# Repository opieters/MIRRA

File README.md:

# MIRRA 

Microclimate Instrument for Real-time Remote Applications

⚠️ This is a research project. Limited testing has been performed and reliability of data storage/sensor readout is not guaranteed. Use with caution. ⚠️

## 3D Designs

The radiation is 3D printed and designed using OpenSCAD. All design files can eb found in `3d_printing`. They can be printed using an extrusion printer, with minimal post-processign (no supports).

## PCB designs

All PCBs are designed with KiCAD and located in the `pcb_boards` directory. Components also contain ordering codes for Mouser and/or Farnell, such that the design is completely rebuilable.

## Embedded Code

The software for the sensor node and gateway are located in the `firmware` folder. The easiest way to build and upload the code is using PlaformIO. 

## Server / web-interface

Use docker-compose to start the webserver and related components (such as MQTT server, graphena...) from the `webserver` folder. Some services are password protected, the passwords are (for now) also included in the docker-compose file.

## Licence

Apache-2.0 License, see LICENSE file.

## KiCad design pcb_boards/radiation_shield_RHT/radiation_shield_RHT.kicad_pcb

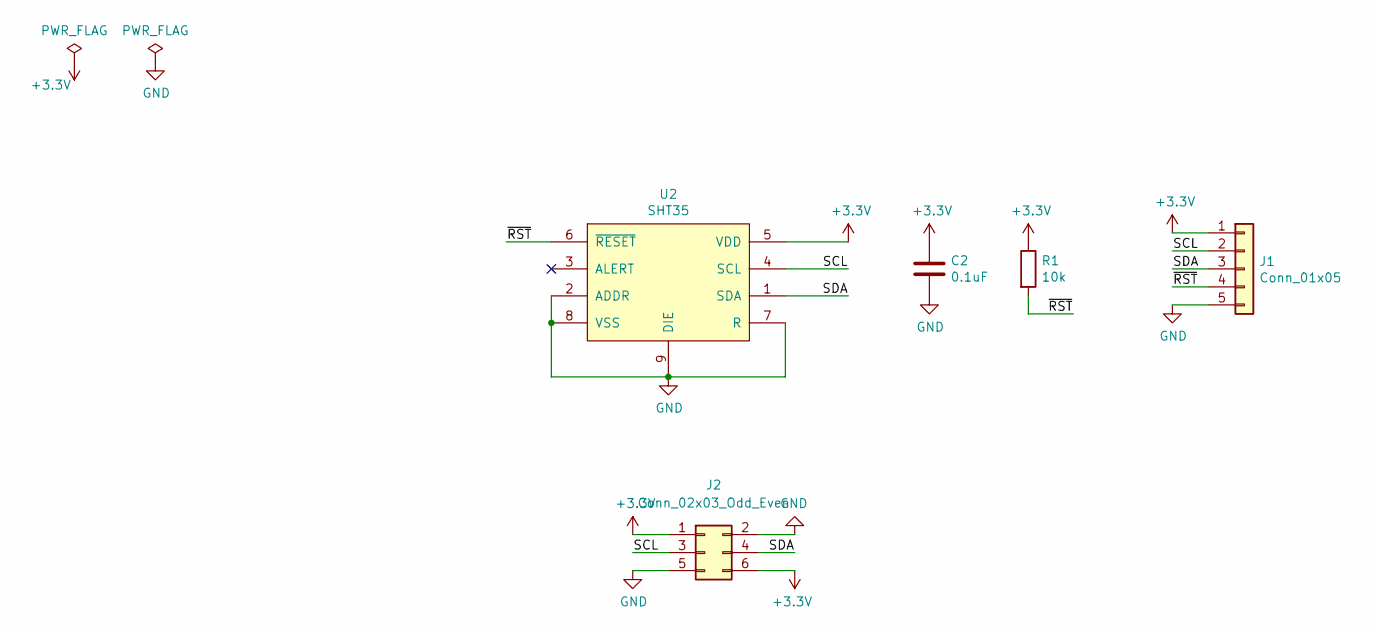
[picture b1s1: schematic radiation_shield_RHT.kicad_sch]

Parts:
C2: 0.1uF; C_0603_1608Metric; Mouser 810-CGA3E2X8R1E104K
J1: Conn_01x05; JST_XH_B05B-XH-A_1x05_P2.50mm_Vertical; Mouser Farnell: 1516281
J2: Conn_02x03_Odd_Even; PinHeader_2x03_P2.54mm_Vertical; Mouser 538-10-88-3061
R1: 10k; R_0603_1608Metric; Mouser 284-APC0603B10K0N
U2: SHT35; 8P-1EP-DFN_2.5x2.5; Mouser 403-SHT35-DIS-F

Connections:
+3V3: C2.1, J1.1, J2.1, J2.6, R1.1, U2.5 (VDD)
/SCL: J1.2, J2.3, U2.4 (SCL)
/SDA: J1.3, J2.4, U2.1 (SDA)
/~RST: J1.4, R1.2, U2.6 (~RESET)
GND: C2.2, J1.5, J2.2, J2.5, U2.2 (ADDR), U2.7 (R), U2.8 (VSS), U2.9 (DIE)

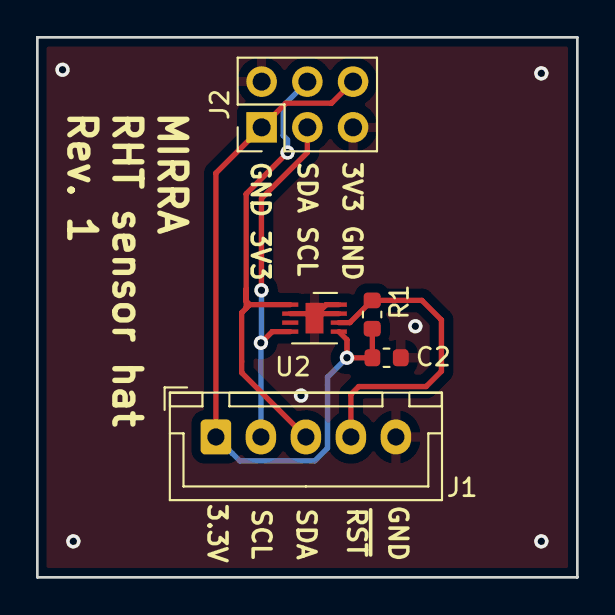
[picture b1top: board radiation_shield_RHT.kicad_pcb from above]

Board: 2 copper layers, 30.0 x 30.0 mm, 5 parts (0 on the bottom side), 5 nets.

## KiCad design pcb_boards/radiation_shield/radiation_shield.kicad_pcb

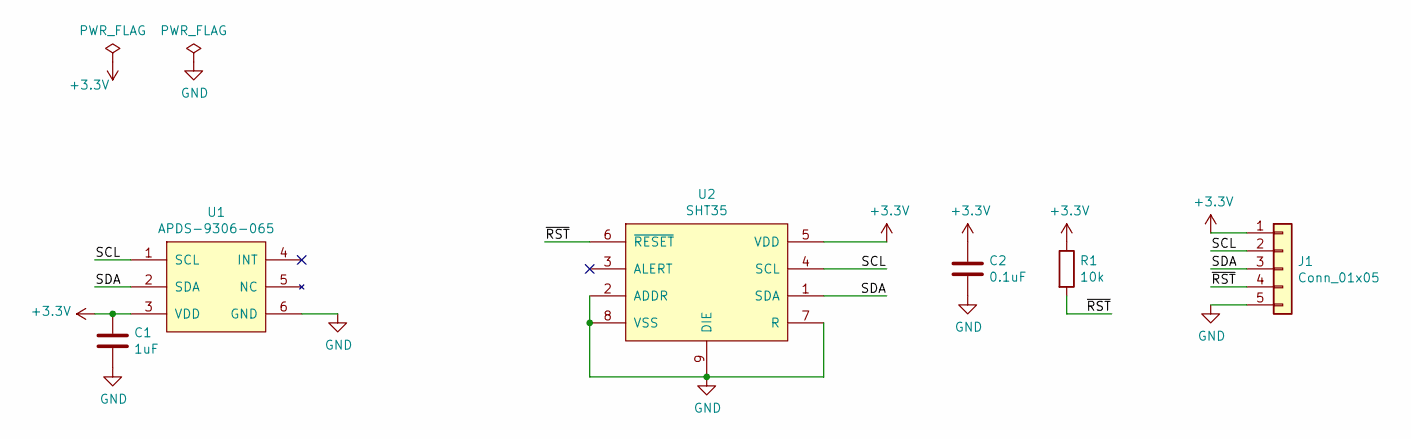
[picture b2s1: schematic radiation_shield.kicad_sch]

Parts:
C1: 1uF; C_0603_1608Metric; Mouser 710-885012206083
C2: 0.1uF; C_0603_1608Metric; Mouser 810-CGA3E2X8R1E104K
J1: Conn_01x05; JST_XH_B05B-XH-A_1x05_P2.50mm_Vertical; Mouser Farnell: 1516281
R1: 10k; R_0603_1608Metric; Mouser 284-APC0603B10K0N
U1: APDS-9306-065; Mouser 630-APDS-9306-065
U2: SHT35; 8P-1EP-DFN_2.5x2.5; Mouser 403-SHT35-DIS-F

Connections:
+3V3: C1.1, C2.1, J1.1, R1.1, U1.3 (VDD), U2.5 (VDD)
/SCL: J1.2, U1.1 (SCL), U2.4 (SCL)
/SDA: J1.3, U1.2 (SDA), U2.1 (SDA)
/~RST: J1.4, R1.2, U2.6 (~RESET)
GND: C1.2, C2.2, J1.5, U1.6 (GND), U2.2 (ADDR), U2.7 (R), U2.8 (VSS), U2.9 (DIE)

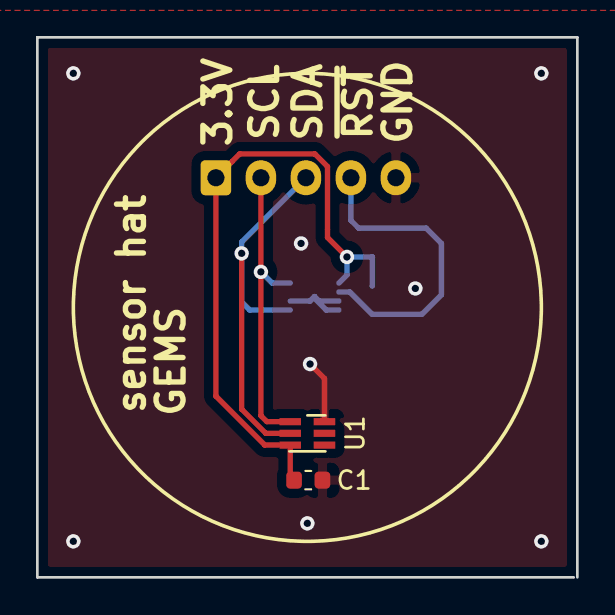
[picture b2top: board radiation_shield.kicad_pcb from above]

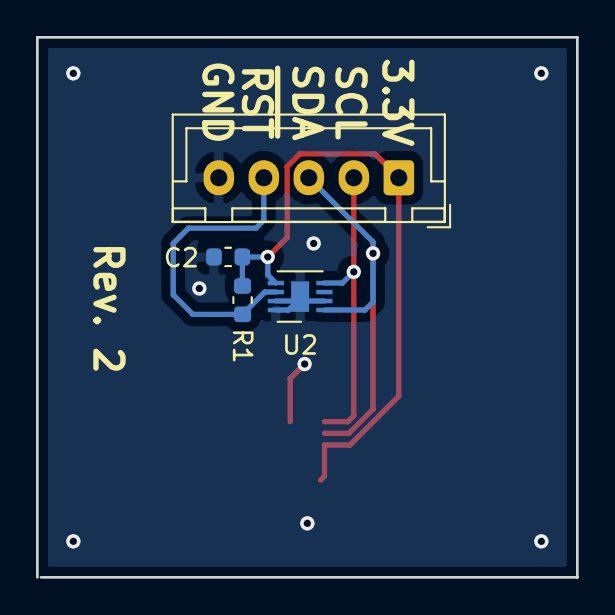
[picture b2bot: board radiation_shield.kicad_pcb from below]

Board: 2 copper layers, 30.0 x 30.0 mm, 6 parts (4 on the bottom side), 5 nets.

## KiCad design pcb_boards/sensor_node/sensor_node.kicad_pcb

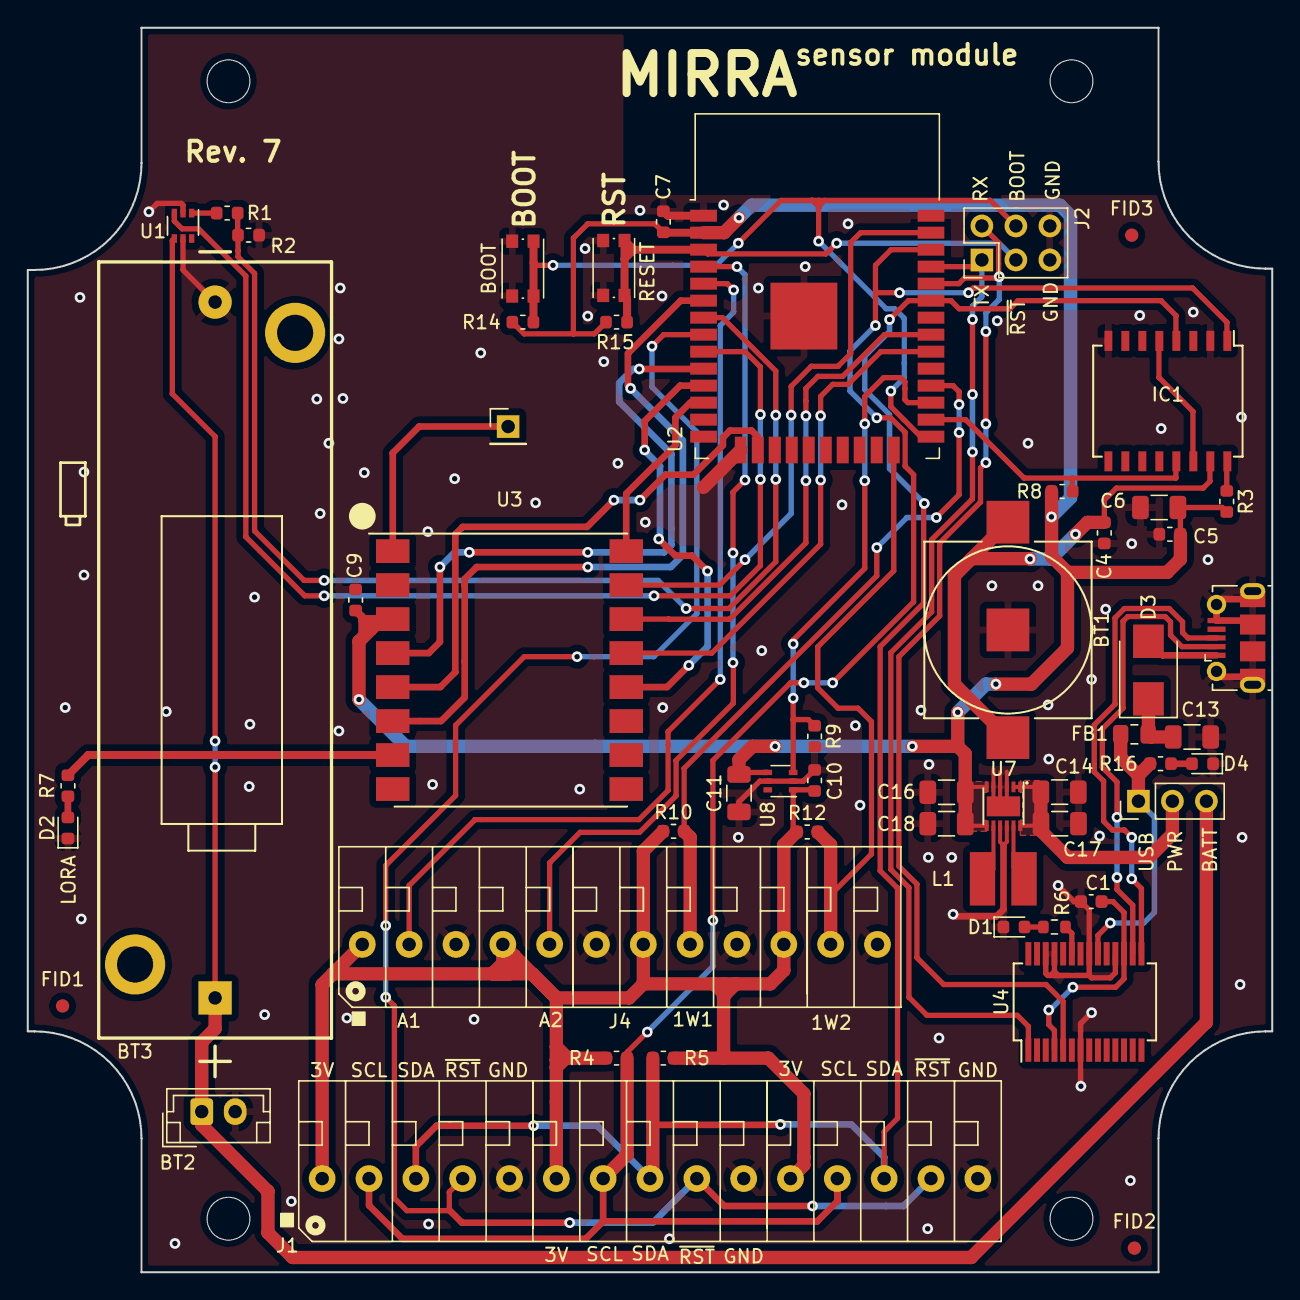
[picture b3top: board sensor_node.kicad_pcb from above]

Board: 2 copper layers, 93.0 x 93.0 mm, 58 parts (0 on the bottom side), 46 nets.

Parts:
AE1: Antenna; PinHeader_1x01_P2.54mm_Vertical
BT1: Battery_Cell; Renata_Battery_Holder_SMTM1125
BT2: Battery_Cell; JST_EH_B02B-EH-A_1x02_P2.50mm_Vertical
BT3: Battery_Cell; Eagle_Battery_Holder_A_12BH311P-GR
C1, C4, C5, C7, C9, C10: 100nF; C_0603_1608Metric
C6, C11: 6.8µF; C_1206_3216Metric
C13, C14, C17: 10uF; C_1206_3216Metric
C16, C18: 22uF; C_1206_3216Metric
D1, D2, D4: LED; LED_0603_1608Metric
D3: D_Schottky; D_SMB
FB1: Ferrite_Bead; L_0805_2012Metric_Pad1.15x1.40mm_HandSolder
FID1, FID2, FID3: Fiducial; Fiducial_1mm_Mask2mm
H1, H2, H3, H4: MountingHole; MountingHole_3.2mm_M3
IC1: PCF2129T; SO16
IO4: BOOT; SW_SPST_KMR2
J1: Screw_Terminal_01x15; TerminalBlock_Phoenix_PTSA-1,2-2-3,5-F-THR-1x15-P3.50mm_45D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
J2: Conn_02x03_Odd_Even; PinHeader_2x03_P2.54mm_Vertical
J3: USB_B_Micro; USB_Micro-B_Molex-105017-0001
J4: Screw_Terminal_01x12; TerminalBlock_Phoenix_PTSA-1,2-2-3,5-F-THR-1x12-P3.50mm_45D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
JP2: Jumper_3_Open; PinHeader_1x03_P2.54mm_Vertical
L1: 2.2uH; L_L4mm_D4mm_H1.8mm
R1, R2, R4, R5, R8, R14, R15: 10k; R_0603_1608Metric
R3: 330R; R_0603_1608Metric
R6: 60R; R_0603_1608Metric
R7, R16: 750R; R_0603_1608Metric
R9: 10M; R_0603_1608Metric
R10, R12: 4.7k; R_0603_1608Metric
RESET1: RESET; SW_SPST_KMR2
U1, U8: SiP32431; SOT-363_SC-70-6
U2: ESP32-WROOM-32
U3: RF-LORA-868-SO; RF-LORA-868-SMT
U4: FT232RL; SSOP-28_5.3x10.2mm_P0.65mm
U7: RP604x; DFN_12_Pin_2.7x3mm_P0.5mm

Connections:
+3.3V: C5.1, C6.2, C7.2, C9.1, C11.1, C16.1, C18.1, R3.2, R8.1, R14.1, R15.1, U2.2 (VDD), U3.3 (VCC), U7.6 (VFB), U7.7 (VOUT), U8.4 (IN)
+BATT: BT2.1 (+), BT3.1 (+), JP2.3 (B), U1.4 (IN)
/A1: J4.2, U2.5 (SENSOR_VN)
/A2: J4.5, U2.4 (SENSOR_VP)
/BATT_M: R1.1, R2.1, U2.7 (IO35)
/BATT_MC: U1.3 (ON/OFF), U2.9 (IO33)
/BBS: IC1.5 (IFS), IC1.14 (BBS)
/BOOT: IO4.1, J2.4, R14.2, U2.25 (IO0)
/D+: J3.3 (D+), U4.15 (USBD+)
/D-: J3.2 (D-), U4.16 (USBD-)
/INT_T: IC1.13 (~INT), R8.2, U2.26 (IO4)
/IRQ: U2.6 (IO34), U3.6 (DIO0)
/MISO: U2.31 (IO19), U3.14 (SDO)
/MOSI: U2.37 (IO23), U3.15 (SDI)
/NSS: U2.12 (IO27), U3.16 (~CS)
/ONE_W1: J4.8, R10.2, U2.28 (IO17)
/ONE_W2: J4.11, R12.2, U2.24 (IO2)
/RX: J2.2, U2.34 (RXD0/IO3), U4.5 (RXD)
/RX_SW: U2.10 (IO25), U3.4 (RX_SW)
/SCK: U2.30 (IO18), U3.13 (SCK)
/SCL: IC1.1 (SCL), J1.2, J1.7, J1.12, R4.1, U2.36 (IO22)
/SDA: IC1.4 (SDA/~CE), J1.3, J1.8, J1.13, R5.1, U2.33 (IO21)
/SPOW: R9.1, U2.27 (IO16), U8.3 (ON/OFF)
/TX: J2.1, U2.35 (TXD0/IO1), U4.1 (TXD)
/TX_SW: U2.16 (IO13), U3.5 (TX_SW)
/~RST_I2C: J1.4, J1.9, J1.14, U2.8 (IO32)
/~RST_RF: U2.11 (IO26), U3.12 (RST)
/~RST: J2.3, R15.2, RESET1.1, U2.3 (EN)
GND: BT1.2 (-), BT2.2 (-), BT3.2 (-), C1.2, C4.1, C5.2, C6.1, C7.1, C9.2, C10.2, C11.2, C13.1, C14.1, C16.2, C17.1, C18.2, D1.1 (K), D2.1 (K), D4.1 (K), IC1.2 (SDI), IC1.8 (VSS), IO4.2, J1.5, J1.10, J1.15, J2.5, J2.6, J3.5 (GND), J3.6 (Shield), J4.3, J4.6, J4.9, J4.12, R2.2, R9.2, RESET1.2, U1.2 (GND), U1.5 (GND), U2.1 (GND), U2.15 (GND), U2.38 (GND), U2.39 (GND), U3.2 (GND), U4.7 (GND), U4.18 (GND), U4.21 (GND), U4.25 (AGND), U4.26 (TEST), U7.3 (PGND), U7.4 (PGND), U7.5 (AGND), U7.9 (PGND), U7.10 (PGND), U7.13 (PAD), U8.2 (GND), U8.5 (GND)
unnamed: AE1.1 (A), U3.1 (ANT)
unnamed: BT1.1 (+), C4.2, IC1.15 (VBAT)
unnamed: C1.1, U4.4 (VCCIO), U4.17 (3V3OUT)
unnamed: C13.2, D3.1 (K), FB1.2
unnamed: D1.2 (A), R6.2
unnamed: D2.2 (A), R7.1
unnamed: D3.2 (A), J3.1 (VBUS)
unnamed: D4.2 (A), R16.1
unnamed: IC1.16 (VDD), R3.1
unnamed: L1.1, U7.11 (BULX)
unnamed: L1.2, U7.8 (BOLX)
unnamed: R1.2, U1.1 (OUT)
unnamed: R6.1, U4.23 (CBUS0)
unnamed: R7.2, U3.7 (DIO1)
VBUS: FB1.1, JP2.1 (A), R16.2, U4.20 (VCC)
VD: C14.2, C17.2, JP2.2 (C), U7.1 (AVIN), U7.2 (CE), U7.12 (PVIN)
VPP: C10.1, J1.1, J1.6, J1.11, J4.1, J4.4, J4.7, J4.10, R4.2, R5.2, R10.1, R12.1, U8.1 (OUT)

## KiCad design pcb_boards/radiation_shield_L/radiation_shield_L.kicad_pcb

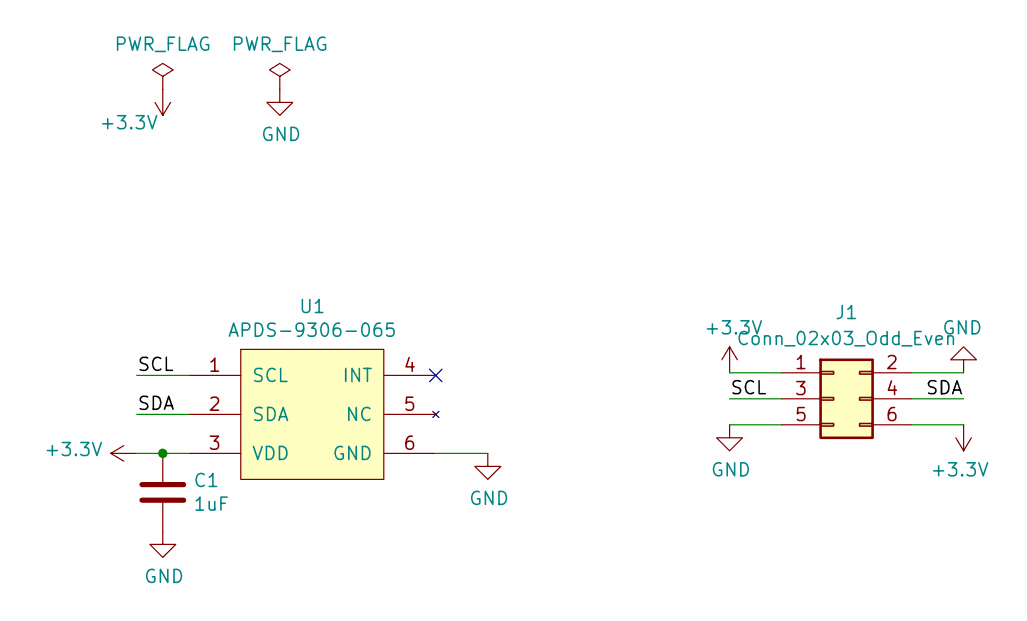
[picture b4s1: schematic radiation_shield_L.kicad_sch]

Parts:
C1: 1uF; C_0603_1608Metric; Mouser 710-885012206083
J1: Conn_02x03_Odd_Even; PinSocket_2x03_P2.54mm_Vertical; Mouser 538-15-44-6806
U1: APDS-9306-065; Mouser 630-APDS-9306-065

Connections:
+3V3: C1.1, J1.1, J1.6, U1.3 (VDD)
/SCL: J1.3, U1.1 (SCL)
/SDA: J1.4, U1.2 (SDA)
GND: C1.2, J1.2, J1.5, U1.6 (GND)

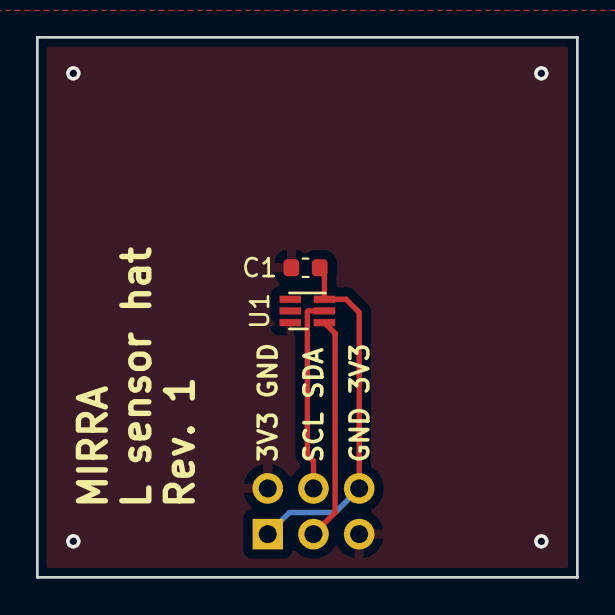
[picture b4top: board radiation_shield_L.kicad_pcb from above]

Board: 2 copper layers, 30.0 x 30.0 mm, 3 parts (1 on the bottom side), 4 nets.

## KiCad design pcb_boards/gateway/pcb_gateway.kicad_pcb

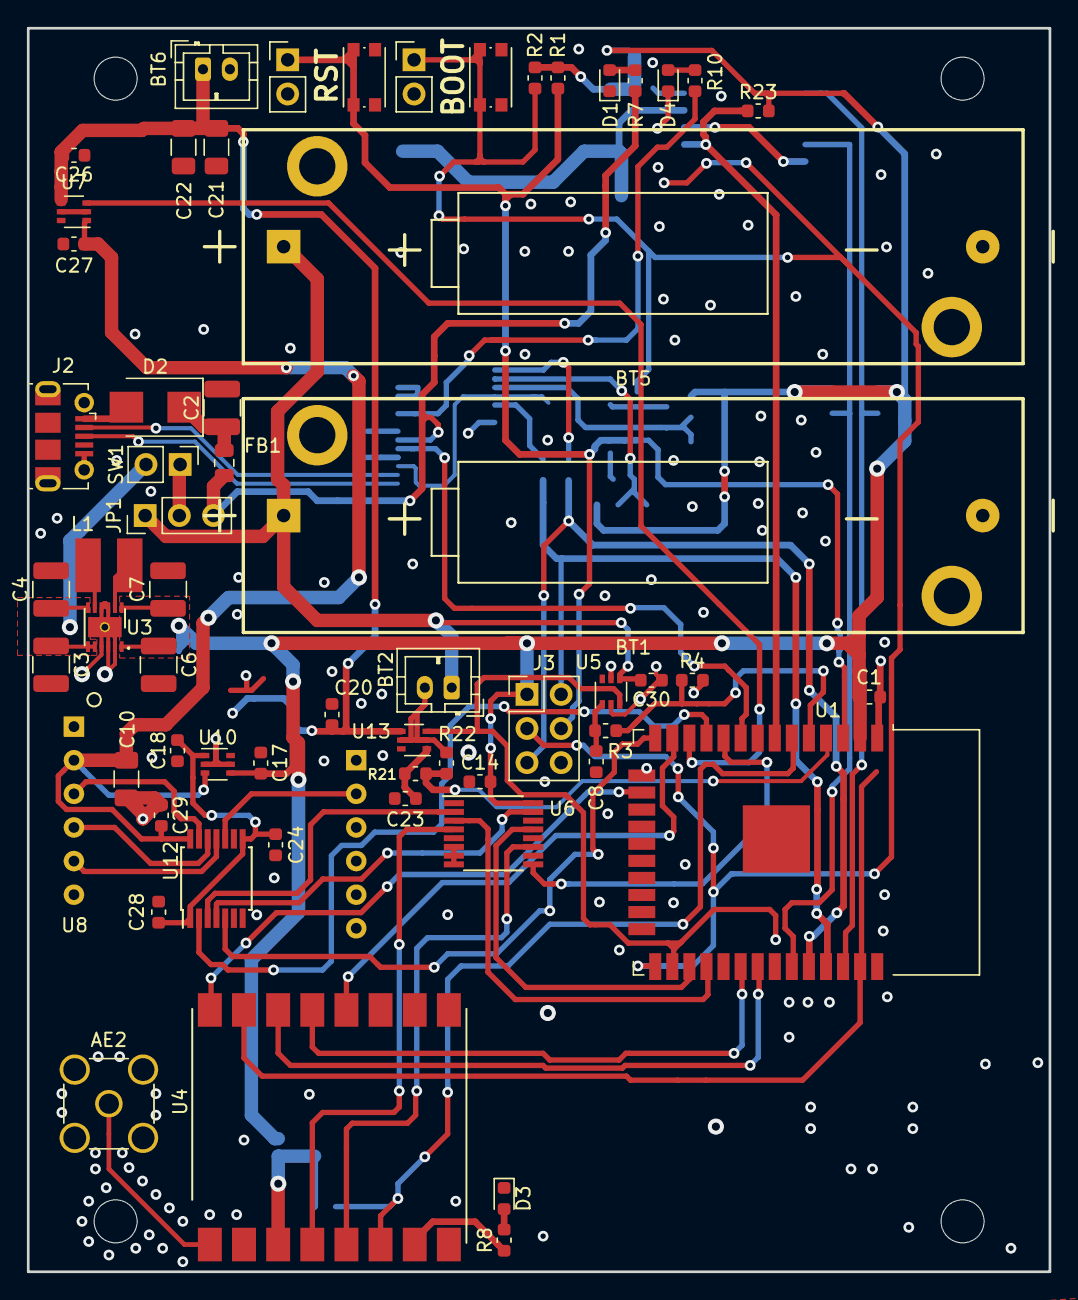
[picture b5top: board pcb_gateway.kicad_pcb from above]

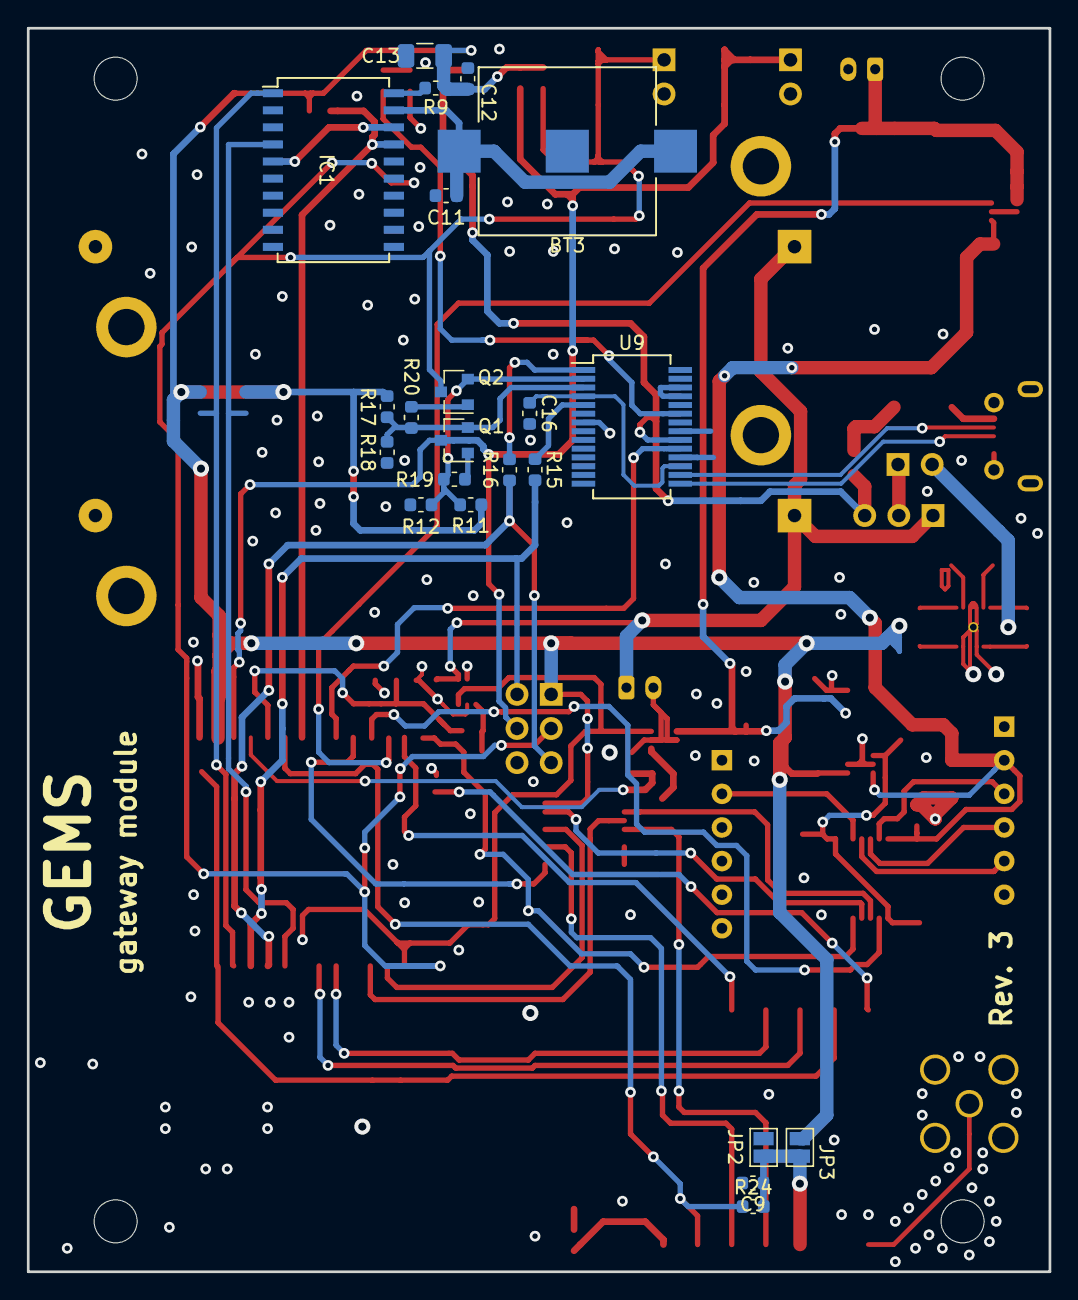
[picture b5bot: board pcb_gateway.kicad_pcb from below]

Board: 2 copper layers, 76.0 x 92.5 mm, 86 parts (23 on the bottom side), 65 nets.

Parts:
AE2: Conn_Coaxial; SMA_Amphenol_901-144_Vertical
BT1, BT5: Battery_Cell; Eagle_Battery_Holder_A_12BH311P-GR
BT2, BT6: Battery_Cell; JST_PH_B2B-PH-K_1x02_P2.00mm_Vertical
BT3: Battery_Cell; Renata_Battery_Holder_SMTM1125
C1, C9, C11, C12, C14, C16, C17, C20, C24, C28, C29: 100nF; C_0603_1608Metric
C2, C3, C4: 10uF; C_1210_3225Metric
C6, C7: 22uF; C_1210_3225Metric
C8, C18, C23, C26, C27, C30: 1uF; C_0603_1608Metric
C10, C21, C22: 4.7uF; C_1206_3216Metric
C13: 6.8uF; C_1206_3216Metric
D1, D3, D4: LED; LED_0603_1608Metric
D2: D_Schottky; D_SMB
FB1: Ferrite_Bead; L_0805_2012Metric
H1, H2, H3, H4: MountingHole; MountingHole_3.2mm_M3
IC1: PCF2129AT; SO20
J2: USB_B_Micro; USB_Micro-B_Molex-105017-0001
J3: Conn_02x03_Counter_Clockwise; PinHeader_2x03_P2.54mm_Vertical
J4, J5: Conn_01x02; PinHeader_1x02_P2.54mm_Vertical
JP1: Jumper_3_Open; PinHeader_1x03_P2.54mm_Vertical
JP2, JP3: Jumper_2_Open; SolderJumper-2_P1.3mm_Open_Pad1.0x1.5mm
L1: 2.2uH; L_L4mm_D4mm_H1.8mm
Q1, Q2: S8050; SOT-23-var
R1, R2, R3, R4, R11, R12, R17, R18, R21, R22, R23, R24: 10k; R_0603_1608Metric
R7, R8: 750R; R_0603_1608Metric
R9: 330R; R_0603_1608Metric
R10: 60R; R_0603_1608Metric
R15, R16: 0R; R_0603_1608Metric
R19, R20: 12k; R_0603_1608Metric
SW1: SW_SPST; PinHeader_1x02_P2.54mm_Vertical
SW2, SW3: SW_Push; SW_SPST_KMR2
U1: ESP32-WROOM-32
U3: RP604x; DFN_12_Pin_2.7x3mm_P0.5mm
U4: RF-LORA-868-SO; RF-LORA-868-SMT
U5, U7, U10, U13: SiP32431; SOT-363_SC-70-6
U6: NLHV4052; TSSOP-16_4.4x5mm_P0.65mm
U8: SIM800L; SIM800L_MODULE
U9: FT232RL; SSOP-28_5.3x10.2mm_P0.65mm
U12: TXS0104E; TSSOP-14_4.4x5mm_P0.65mm

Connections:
+3V3: C1.2, C6.1, C7.1, C12.2, C13.2, C14.2, C17.2, J3.1, JP3.2, R1.2, R2.2, R9.1, R11.2, R17.2, R23.1, U1.2, U3.6, U3.7, U6.16, U10.4
+4V: BT6.1, C20.2, C21.2, C22.2, C26.2, U7.4, U13.4
+BATT: BT1.1, BT2.1, BT5.1, C30.2, JP1.1, U5.4
/BATT_M: R3.1, R4.1, U1.5
/BOOT: J3.3, J5.1, Q2.3, R2.1, SW3.1, U1.25
/D+: J2.3, U9.15
/D-: J2.2, U9.16
/DTR: Q2.1, R11.1, R12.2, R19.1, U9.2
/DTR_SIM: U8.11, U12.10
/DTR_SIM_LV: U1.14, U12.5
/EN_BM: U1.26, U5.3, U13.3
/EN_ESP: J3.4, J4.1, Q1.3, R1.1, SW2.1, U1.3
/EN_GPRS: U1.12, U7.3
/LORA_PWR: C9.2, JP2.2, JP3.1, R24.2, U4.3
/MISO: U1.31, U4.14
/MON_LIPO: R21.2, R22.1, U1.4
/MOSI: U1.37, U4.15
/M_SEL0: U1.10, U6.9
/REG_4V: C10.1, C27.2, C29.2, U7.1, U8.2, U10.3, U12.14
/RF_IRQ: R24.1, U1.6, U4.6
/RST_RF: U1.13, U4.12
/RST_SIM: U8.3, U12.13
/RST_SIM_LV: U1.11, U12.2
/RTS: Q1.1, R17.1, R18.2, R20.2, U9.3
/RX: J3.5, R16.1, U1.34
/RX0: R15.2, U9.5
/RX2: U1.27, U6.13
/RXD_SIM: U8.4, U12.12
/RXD_SIM_LV: U6.2, U12.3
/RX_LORA: U4.4, U6.4
/SCL: IC1.1, U1.36
/SCLK: U1.30, U4.13
/SDA: IC1.4, U1.33
/TX: J3.2, R15.1, U1.35
/TX0: R16.2, U9.1
/TX2: U1.28, U6.3
/TXD_SIM: U8.5, U12.11
/TXD_SIM_LV: U6.15, U12.4
/TX_LORA: U4.5, U6.11
/VCC3.3_GSM: C18.2, C24.2, C28.2, U10.1, U12.1, U12.8
/~RST_FTDI: U1.9, U9.19
/~SS_RF: U1.16, U4.16
/~T_INT: IC1.17, R23.2, U1.7
GND: AE2.2, BT1.2, BT2.2, BT3.2, BT5.2, BT6.2, C1.1, C2.2, C3.2, C4.2, C6.2, C7.2, C8.1, C9.1, C10.2, C11.1, C12.1, C13.1, C14.1, C16.2, C17.1, C18.1, C20.1, C21.1, C22.1, C23.1, C24.1, C26.1, C27.1, C28.1, C29.1, C30.1, D1.1, D3.1, D4.1, IC1.2, IC1.8, J2.5, J2.6, J3.6, J4.2, J5.2, R4.2, R12.1, R18.1, R22.2, SW2.2, SW3.2, U1.1, U1.15, U1.38, U3.3, U3.4, U3.5, U3.9, U3.10, U3.13, U4.2, U5.2, U5.5, U6.6, U6.7, U6.8, U6.10, U7.2, U7.5, U8.6, U9.7, U9.18, U9.21, U9.25, U9.26, U10.2, U10.5, U12.7, U13.2, U13.5
unnamed: AE2.1, U4.1
unnamed: BT3.1, C11.2, IC1.19
unnamed: C2.1, D2.1, FB1.2
unnamed: C8.2, R3.2, U5.1
unnamed: C16.1, U9.4, U9.17
unnamed: C23.2, R21.1, U13.1
unnamed: D1.2, R7.2
unnamed: D2.2, J2.1
unnamed: D3.2, R8.2
unnamed: D4.2, R10.2
unnamed: IC1.5, IC1.18
unnamed: IC1.20, R9.2
unnamed: JP1.2, SW1.1
unnamed: L1.1, U3.11
unnamed: L1.2, U3.8
unnamed: Q1.2, R19.2
unnamed: Q2.2, R20.1
unnamed: R8.1, U4.7
unnamed: R10.1, U9.23
VBUS: FB1.1, JP1.3, R7.1, U9.20
VD: C3.1, C4.1, SW1.2, U3.1, U3.2, U3.12

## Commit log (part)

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2021-04-23 3D printing files.
2021-04-23 PCB designs.
2021-04-23 Add README
2021-05-04 Docker compose file of management interface.
2021-05-04 Ignore files.
2021-05-04 Updated ignore files.
2021-05-04 Add file that was previously ignored.
2021-05-04 Corrected JS en CSS import.
2021-05-04 Fix typo.
2021-05-04 Add vendor packages install script.
2021-05-25 Rename project based on feedback.
2021-06-07 Add firmware and update PCBs
2021-06-07 Romove old file.
2021-10-27 Update PCB.
2021-10-27 ignore sch-bak file.
2021-11-27 New routing design.
2021-11-27 Add Mouser order codes.
2022-02-21 Updated components.
2022-02-21 Fix AT.
2022-11-08 Script to decode serial data storage format and dump as CSV
2022-11-09 Possible bug fixes for ESPCam readout.
2022-11-15 Update README.
2023-01-06 Add Python script to decode serial data.
2023-02-28 Push latest version
2023-03-04 fix(docker+web): docker configuration now working, vendor files added back
2023-03-09 fix(pio)
2023-03-09 Revert "fix(pio)"
    This reverts commit 3e3390f8a5e87cb6f62c364a8fa9d39f80e26e7d.
2023-03-12 Add modified Arduino-OWI library, readd .pio to gitignore
2023-03-12 Remove Arduino-OWI dependency from ESPCam
2023-03-21 Add logging utility This allows for file-based logging in the field. Different log levels allow for granular control of message importance / severity. This should replace all "Serial.print(...)" call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
2023-03-21 Smarter buffer initialisation
2023-03-21 Remove old CommCommand/Int conversions
2023-03-21 Remove empty 'Storage' library
2023-03-23 Further refactoring Mostly unifying the message objects, neatly organising them and associated functionality into classes. Does not build!
2023-03-23 Bugfix in MACAddress::toString
2023-03-27 Add TODO idea
2023-03-27 Greatly optimise Logger
2023-03-28 Update SensorValue to make use of packed structs
2023-03-28 Implement autodeletion in logging
2023-03-31 Add format string/variable arg print to Logger
2023-03-31 Switch from LoraLib to RadioLib
2023-03-31 Add default constructor to MACAddress
2023-04-01 Move pin config to config.h
2023-04-01 Remove unused 'cmd' filter from receiveMessage
2023-04-11 Change tag types to unsigned
2023-04-11 Change LoRaModule inheritance to public
2023-04-11 Remove redudant SensorNode.h
2023-04-12 Add message type filtering to receiveMessage
2023-04-12 Implement discovery
2023-04-17 Further implement gateway.cpp
2023-04-23 latest update
2023-05-01 Fix compile error: default args
2023-05-01 Provide definition for MACAddress:str_buffer
2023-05-01 Properly cast tag type
2023-05-01 Reimplement base behaviour Huge overhaul of gateway.cpp Main.cpp reduced to 'startup script' Also start work on UART commands
2023-05-01 Finalise UART commands
2023-05-02 Slightly refactor RTC code
2023-05-02 Put global initialisations outside of gateway.cpp
2023-05-03 Change pin assignemnts to reflect sensor board
2023-05-03 Fix various issues with gateway behaviour Fixes many breaking bugs, further implements UART commands
2023-05-03 Edit 'reference years', fix some bugs
2023-05-03 Remove RTC, fix nullptr exception, remove DIO1 pin
2023-05-04 change MQTT server
2023-05-04 Fix mday / month adjustment bug
2023-05-04 Check WiFi status before NTP
2023-05-04 Remove redundant debug serial call
2023-05-04 Add uploadPeriod declaration
2023-05-04 Deployment stuff
2023-05-05 Implement printhex, fix error check in commPeriod
2023-05-05 Create sensor node base files
2023-05-05 Adjuts some includes
2023-05-05 Fix forgotten semicolons in TimeConfig getters
2023-05-06 Optimize init lists, logfile handling
2023-05-06 Optimize init list, remove unused time_buf
2023-05-06 Implement MIRRAModule in gateway
2023-05-07 Fixed some typos in sensor_types
2023-05-08 Adjust some comm parameters
2023-05-08 Add command phase entry to commandPhase()
2023-05-08 Add DATA_ACK, SENDOR_DATA_LAST message types
2023-05-08 Remove old SensorNode code
2023-05-08 Properly initialise nextComm/SampleTime
2023-05-08 Add returns to processCommands
2023-05-09 Fix strcmps in processCommands
2023-05-11 add get_all_sensors_from_location
2023-05-11 added provisionary sensor_overview dropdown item
2023-05-11 Remove trailing whitespace in wifi command
2023-05-11 Adjust LoRa settings/macros
2023-05-11 Look for LoRa damaged header error
2023-05-11 First version sensor_overview
    only shows all locations and corresponding nodes, no other functionality
2023-05-11 Temporarily add RadioLib as git submodule
2023-05-11 Point RadioLib submodule to own fork
2023-05-11 Wait until timeout, possibly REPEAT when CRC fails
2023-05-11 MQTT
2023-05-14 Close sensor data file after pruning Also prune right after a comm period
2023-05-15 Templatise send/receive functions to avoid slicing
2023-05-15 nodeCommPeriod: only prelisten for first message
2023-05-15 Declare sample/comm period
2023-05-15 Limit gateway comm period to MAX_SENSOR_MESSAGES
2023-05-16 Implement samplePeriod, commPeriod
2023-05-16 DB update
2023-05-16 Pass header by value (consistent with subclasses)
2023-05-16 MAC to string in printf
2023-05-16 to_data -> toData, make header constructor uniform
2023-05-16 set allow_embedding to true
2023-05-16 Remove unnescessary casts in _SleepUntil
2023-05-16 Adjust UART_PHASE_ENTRY_PERIOD
2023-05-16 Correct various errors in SensorNode::commPeriod
2023-05-16 Fix commandPhase
2023-05-16 Revert processCommands to virtual function
2023-05-16 Add error when deep sleep time is zero/negative
2023-05-16 Improve comm period scheduling
2023-05-16 Changed get_all_locations to function with the new layout of the database
    In the database, the foreign key "location_id" was removed from forests and replaced by a foreign key "forest_id" in locations. As there are supposed to be multiple locations within 1 forest, this is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
2023-05-16 removed location_id from add_forest
    see description of previous commit
2023-05-16 Correct nodeCommPeriod decleration, timeConfig
2023-05-16 fixed typo
2023-05-16 Make 'last' flag last bit of message type
2023-05-16 Correct more behavioural errors in node commPeriod
2023-05-16 Use integers instead of floats for deepSleep
2023-05-16 Send TIME_ACK to gateway at end of comm period
2023-05-16 Remove decrement of repeat attempts
2023-05-16 Correct MAC dest of ACK_TIME
2023-05-16 Add some extra logging to gateway's comm period
2023-05-16 Append samples to data instead of overwriting
2023-05-16 Apostrophe :|
2023-05-16 Adjust logs, remove redundant reset
2023-05-16 Add some more logging in uploadPeriod
2023-05-16 Some more logging in gateway comm period
2023-05-16 Edit node constructor so intervals get initialised
2023-05-17 Remove storeNode, adjust nodesFromFile
2023-05-17 Also print desired source MAC address
2023-05-17 Change file to reflect new database layout
2023-05-17 Changed file to reflect new database layout
2023-05-17 MQTT update (since database changes)
2023-05-17 init.sql update
2023-05-17 Webserver overhaul pt. 2
2023-05-17 Adjust WAKE_BEFORE_COMM_PERIOD
2023-05-17 Move good night message before SPIFFS unmounting
2023-05-17 Less excessive logging during WiFi connect
2023-05-17 Correct WiFi connect password
2023-05-17 Avoid reinitialisation of ssid/pass to default
2023-05-17 Show # of received messages
2023-05-17 Fix stack smashing SensorDataMessage constructor no longer called on uninitialised buffer
2023-05-18 Pass own MAC by reference
2023-05-18 Introduce MQTT macros
2023-05-18 Increase MQTT buffer size from 256 bytes The prefix seems to be counted: some publishes were longer than allowed.
2023-05-18 Adjust max messages to send Wakeup just before comm period
2023-05-18 Implement WAKE_BEFOE_COMM_PERIOD in sensor node
2023-05-20 Lower repeat attempts, lower coding rate 8 -> 6
2023-05-21 Remove redunant src folders
2023-05-21 Some more library movement
2023-05-22 Refactor sensors and sampling
2023-06-05 Add README.md to firmware folder
2023-07-11 Add .clang-format
2023-07-11 Custom partitioning
2023-07-11 Unify processCommands syntax in gateway
2023-07-12 Remove/move some unused variables
2023-07-12 Remove ArduinoOWI dependency
2023-07-12 Fix Sensor's virtual destructor
2023-07-12 Correct SensorValue retrieval to new interface
2023-07-14 Streamline logging some more Go wild with templates for safe printf Remove NTPClient dependency Properly initialise system time
2023-07-14 Remove AsyncAPDS9306 from ESPCam lib
2023-07-17 Add touch command
2023-07-17 Fix lingering bugs in logging lib
2023-07-19 Use name() instead of path() in pruneSensorData
2023-07-19 Prepare schedule system for OTA parameter updates
2023-07-19 Extract print from printv
2023-07-23 Refactor sensor scheduling
2023-07-24 Further adjust sensor node scheduling
2023-07-24 Adjust ESPCam 'adaptive' sampling schedule
2023-07-24 initSensors before sampleAll in printSample
2023-07-25 Make pins constexpr
2023-07-25 Clean up sunriseTable
2023-07-25 Add ESPCam to sensornode
2023-07-25 Move ESPCamCodes to own mini library
2023-07-25 Clean up ESPCam code, introduce timeout
2023-07-25 Fix PSRAM issue, change pin to 13
2023-07-26 Properly initialise peripheral power Also extract graceful shutdown into end()
2023-07-26 Add debug mesage detailing time config
2023-07-26 Fix various lingering comm/scheduling issues
2023-07-27 Revert back to GPIO12 as UART pin
2023-07-27 Optimise pruneSensorData
2023-07-27 Fix sunriseTable
2023-07-27 Fix infinite recursion
2023-07-30 Add printschedule command
2023-07-30 Add config for actual gateway PCB
2023-07-30 Adjust sunrise table
2023-07-30 Fix command line buffer overflow
2023-07-30 Rework command phase entry
2023-07-30 Adjust logging to file logic
2023-07-31 Fix logging
2023-07-31 Make default comm/sample periods consistent
2023-07-31 Update firmware README.MD with new commands
2023-07-31 Harmonise lightSleepUntil
2023-08-12 Remove desiredType members
2023-08-12 Add getSysTime function, avoid Wnarrowing
2023-08-12 Add documentation
2023-08-12 Make sent buffer const
2023-08-12 Add documentation to RTC module Avoid more Wnarrowing with rtc.getSysTime Camel casing in MIRRAPins
2023-08-13 Add documentation to LoRaModule
2023-08-13 Adds logging documentation
2023-08-13 Adjust SoilTemperatureSensor doc
2023-08-14 Camel case
2023-08-14 Casing
2023-08-14 More accurate naiveTimeConfig
2023-08-16 Add discoveryloop to README.MD
2023-08-16 Set production defaults
2023-08-16 Alter ESPCamCodes values
2023-08-16 Add include guard
2023-08-16 Add logging / commands to ESPCam, clean up
2023-08-18 Add max node size guard to discoveryLoop
2023-08-20 Relax comm period wait requirements
2023-08-20 Use end() before entering deep sleep
2023-08-20 Remove performance-crippling logfile flushing
2023-08-20 Do not remove data file on reset
2023-08-31 Update docker-compose.yml
    Fix graphana user UID.
2023-08-31 Update grafana.ini
    Change HTTPS to HTTP to make testing easier.
2023-09-18 Slightly update README.md
2023-09-21 Formatting
2023-09-21 Quick fix compile error in discoveryLoop
2023-09-21 Add some more gateway documentation
2023-10-12 New PDB version.
    sensor node: added FTDI chip for USB comms
    sensor node: implemented page feedback
    sensor node: remove aerial, and SMA connector, update interfacing and RTC
    sensor hat: update to two PCBs for reduced thermal conductivity
